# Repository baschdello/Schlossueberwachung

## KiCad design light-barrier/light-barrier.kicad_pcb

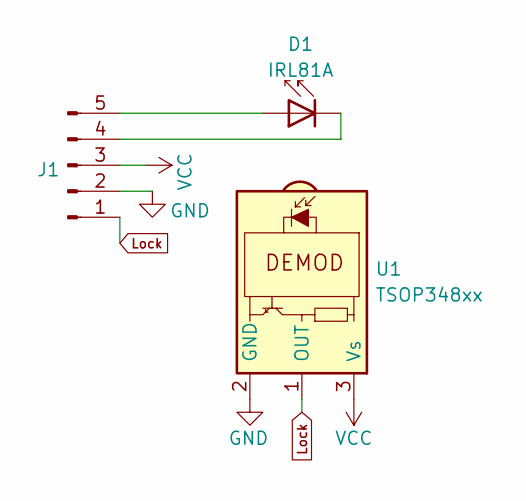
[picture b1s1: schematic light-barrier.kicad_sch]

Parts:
D1: IRL81A; LED_SideEmitter_Rectangular_W4.5mm_H1.6mm
J1: Conn_01x05_Male; PinHeader_2x03_P1.27mm_Vertical
U1: TSOP348xx; Vishay_MOLD-3Pin

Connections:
GND: J1.2, U1.2 (GND)
Lock: J1.1, U1.1 (OUT)
unnamed: D1.2 (A), J1.5
unnamed: D1.1 (K), J1.4
VCC: J1.3, U1.3 (Vs)

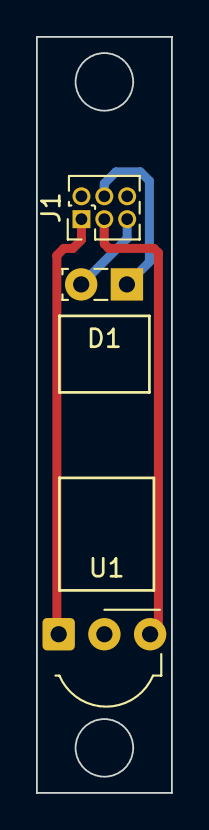
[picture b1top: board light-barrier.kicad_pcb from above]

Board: 2 copper layers, 7.5 x 42.0 mm, 3 parts (0 on the bottom side), 5 nets.

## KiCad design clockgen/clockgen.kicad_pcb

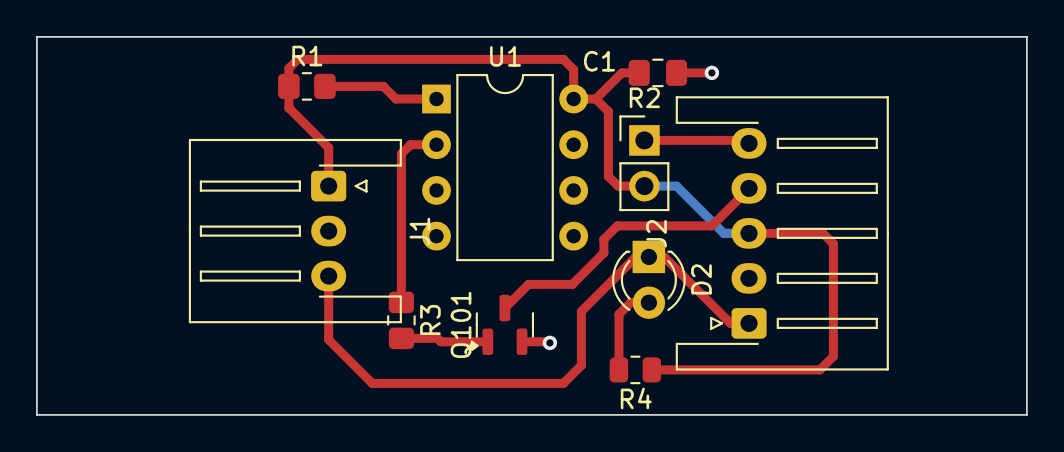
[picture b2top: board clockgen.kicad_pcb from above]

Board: 2 copper layers, 55.0 x 21.0 mm, 10 parts (0 on the bottom side), 9 nets.

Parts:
C1: 100n; C_0805_2012Metric_Pad1.18x1.45mm_HandSolder
D2: LED; LED_D3.0mm
J1: Conn_01x03_Male; JST_XH_S3B-XH-A-1_1x03_P2.50mm_Horizontal
J2: Conn_01x05_Male; JST_XH_S5B-XH-A-1_1x05_P2.50mm_Horizontal
Q101: BC847; SOT-23
R1: 10k; R_0805_2012Metric_Pad1.20x1.40mm_HandSolder
R2: R; PinHeader_1x02_P2.54mm_Vertical
R3: 1k; R_0805_2012Metric_Pad1.20x1.40mm_HandSolder
R4: 220; R_0805_2012Metric
U1: ATtiny13A-P; DIP-8_W7.62mm

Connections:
Emitter1-Anode: J2.5, R2.1
Emitter1-Cathode: J2.4, Q101.3 (C)
GND: C1.2, J1.2, J2.2, Q101.2 (E), U1.4 (GND)
Lock: D2.1 (K), J1.3, J2.1
unnamed: D2.2 (A), R4.2
unnamed: Q101.1 (B), R3.2
unnamed: R3.1, U1.2 (PB3)
unnamed: R1.2, U1.1 (~RESET/PB5)
VCC: C1.1, J1.1, J2.3, R1.1, R2.2, R4.1, U1.8 (VCC)

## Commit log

2024-07-04 restructuring
2024-07-04 added pin description for J2
2025-02-04 modified connector placing
2025-02-06 cleanup
